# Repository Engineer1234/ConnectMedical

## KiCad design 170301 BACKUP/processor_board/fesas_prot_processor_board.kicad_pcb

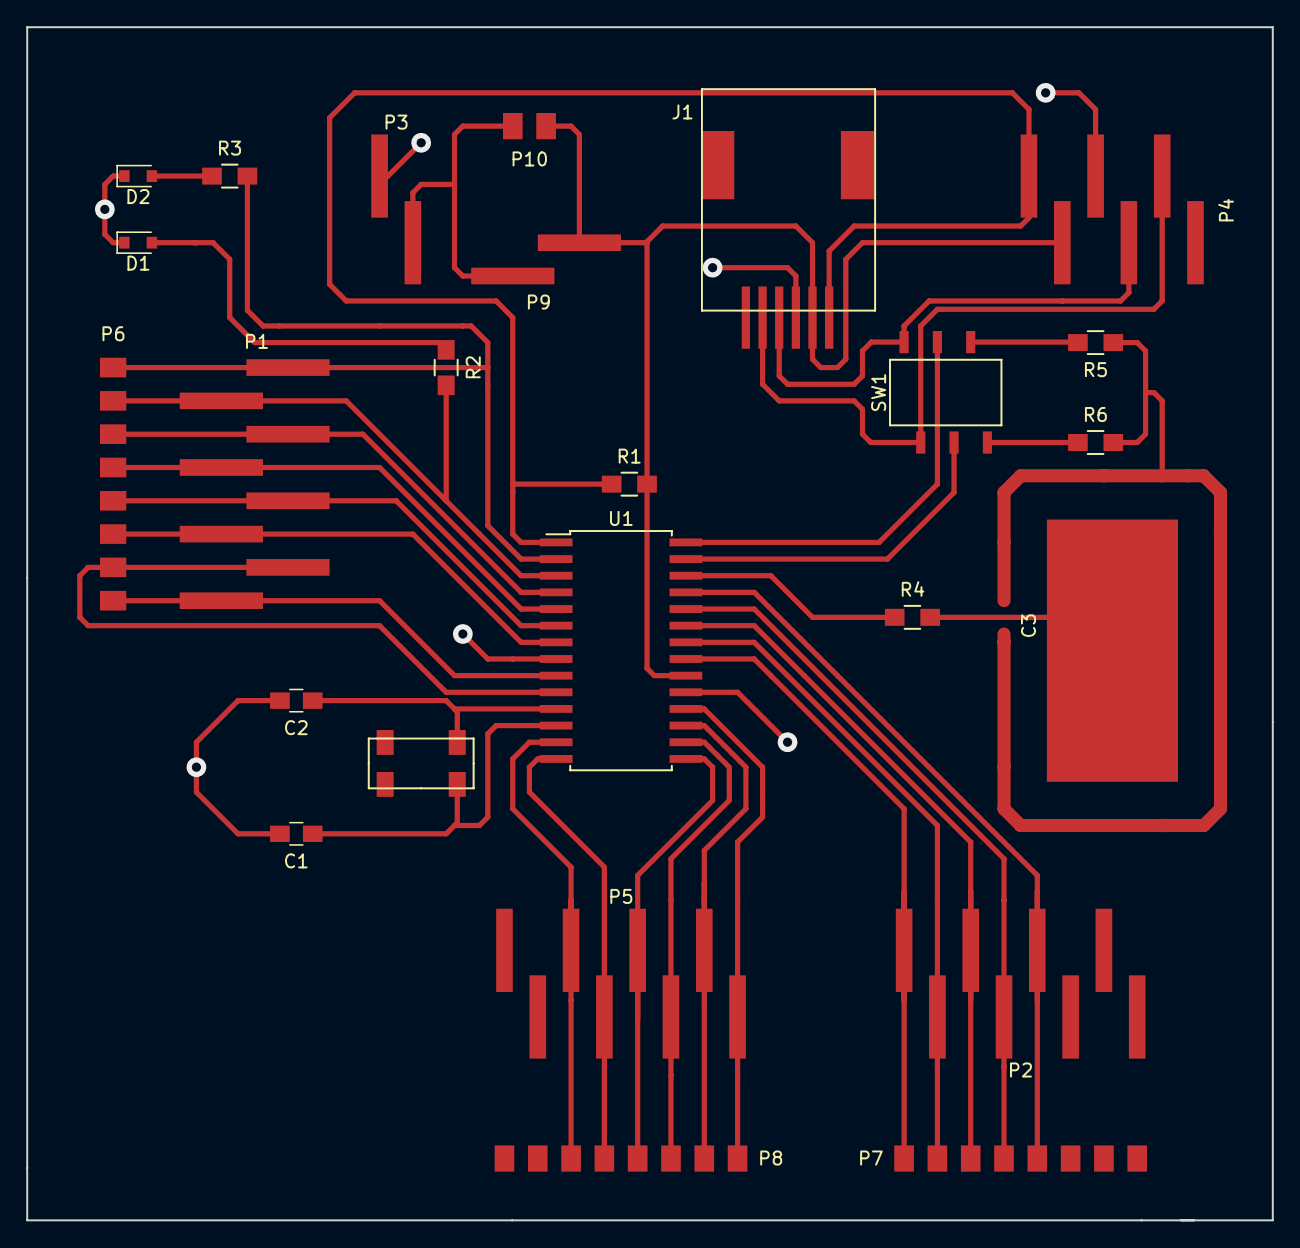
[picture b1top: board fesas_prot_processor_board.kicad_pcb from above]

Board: 2 copper layers, 95.0 x 91.0 mm, 25 parts (0 on the bottom side), 36 nets.

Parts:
C1, C2: 5pF; C_0805_HandSoldering
C3: cap_sense_pad; Capsense_Pad
D1, D2: LED; D_0805
J1: RJ11; RJ11_SMD_Socket
P1, P2, P5: CONN_01X08; Sullins_SMD_pin_header_1x8_GBC36SABN-M30
P3, P9: CONN_01X02; Sullins_SMD_pin_header_1x2_GBC36SABN-M30
P4: CONN_01X06; Sullins_SMD_pin_header_1x6_GBC36SABN-M30
P6, P7, P8: CONN_01X08; wire_solder_pad_2.54mm_1x8
P10: CONN_01X02; wire_solder_pad_2.54mm_1x2
R1: 50k; R_0805_HandSoldering
R2, R3, R4, R5, R6: R; R_0805_HandSoldering
SW1: NKKswitches_G3T22AP; NKKSwitches_G3T22AP
U1: PIC16(L)F1512-I/SO; SOIC-28W_7.5x17.9mm_Pitch1.27mm
Y1: Abracon_ABS25

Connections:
/CAP_SENSOR: R4.1, U1.26
/Guard_trace: R5.1, R6.2
/MCLR/Vpp: J1.1, P4.1, R1.1, U1.1
/PGC(ICSPCLK): J1.5, P4.5, SW1.3
/PGD(ICSPDAT): J1.4, P4.4, SW1.6
GND: C1.2, C2.2, D1.1, D2.1, J1.3, P3.1, P4.3, U1.8, U1.19
unnamed: C1.1, U1.12, Y1.4
unnamed: C2.1, U1.11, Y1.1
unnamed: C3.1, R4.2
unnamed: D1.2, R2.1
unnamed: D2.2, R3.1
unnamed: P1.1, P6.1, U1.9
unnamed: P1.2, P6.2, U1.10
unnamed: P1.3, P6.3, U1.7
unnamed: P1.4, P6.4, U1.6
unnamed: P1.5, P6.5, U1.5
unnamed: P1.6, P6.6, U1.4
unnamed: P1.7, P6.7, R2.2, U1.3
unnamed: P1.8, P6.8, R3.2, U1.2
unnamed: P2.4, P7.4, U1.25
unnamed: P2.5, P7.5, U1.24
unnamed: P2.6, P7.6, U1.23
unnamed: P2.7, P7.7, U1.22
unnamed: P2.8, P7.8, U1.21
unnamed: P5.3, P8.3, U1.13
unnamed: P5.4, P8.4, U1.14
unnamed: P5.5, P8.5, U1.15
unnamed: P5.6, P8.6, U1.16
unnamed: P5.7, P8.7, U1.17
unnamed: P5.8, P8.8, U1.18
unnamed: P3.2, P9.1, P10.2
unnamed: R5.2, SW1.4
unnamed: R6.1, SW1.1
unnamed: SW1.2, U1.27
unnamed: SW1.5, U1.28
VDD: J1.2, P4.2, P9.2, P10.1, R1.2, U1.20

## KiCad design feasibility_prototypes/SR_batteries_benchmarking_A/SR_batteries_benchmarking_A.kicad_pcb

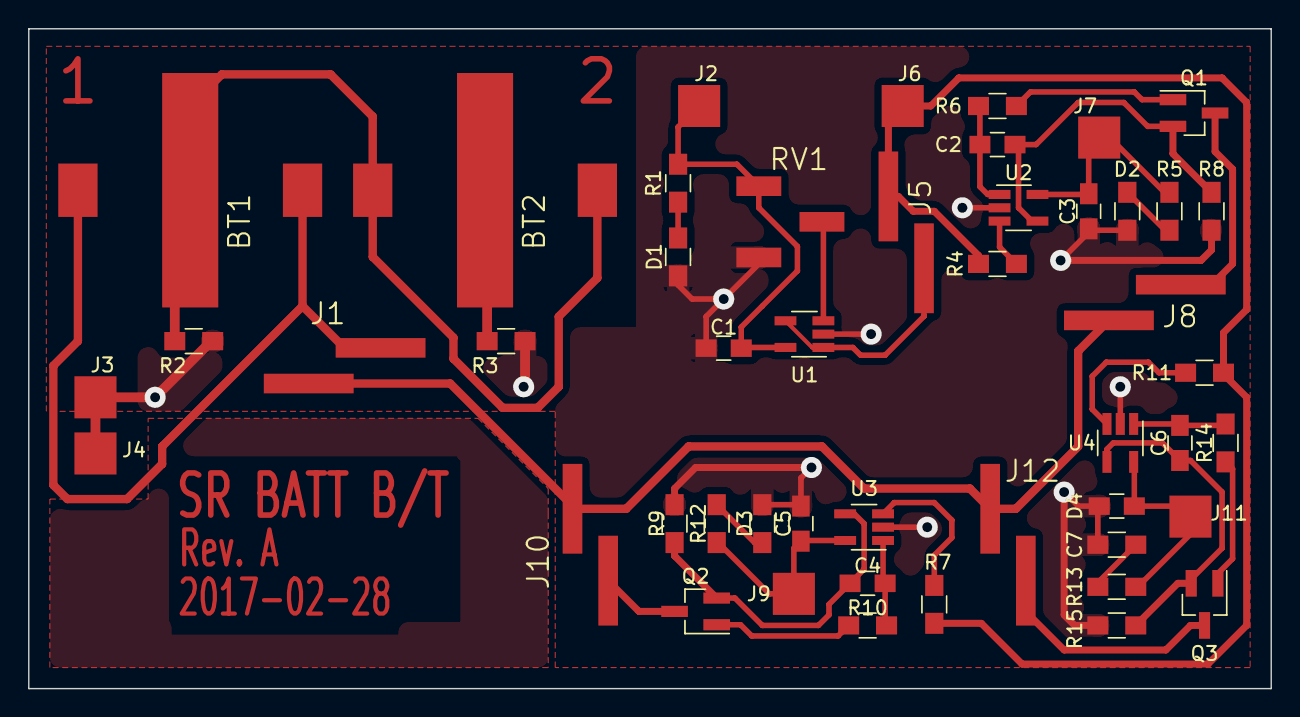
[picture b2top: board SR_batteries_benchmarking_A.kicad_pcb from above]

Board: 2 copper layers, 88.5 x 47.0 mm, 48 parts (0 on the bottom side), 31 nets.

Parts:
BT1: Cell1; proto_sm_coin_cell_holder-2996-2993
BT2: Cell2; proto_sm_coin_cell_holder-2996-2993
C1, C3, C5, C7: 0.1u; C_0805_HandSoldering
C2, C4, C6: C; C_0805_HandSoldering
D1: RED; R_0805_HandSoldering
D2: WHT; R_0805_HandSoldering
D3: GRN; R_0805_HandSoldering
D4: YLW; R_0805_HandSoldering
J1: Current Measurement; proto_smd_header-1x2-2.54mm-G_C__SABN_M30
J2: EN_POT; proto_smd_pad-sq.-3mm
J3, J4: GND; proto_smd_pad-sq.-3mm
J5, J8, J10, J12: Jumper; proto_smd_header-1x2-2.54mm-G_C__SABN_M30
J6: VIN; proto_smd_pad-sq.-3mm
J7: EN_HIGH_CURR; proto_smd_pad-sq.-3mm
J9: EN_LOW_CURR; proto_smd_pad-sq.-3mm
J11: EN_MED_CURR; proto_smd_pad-sq.-3mm
Q1, Q2, Q3: BSH103; SOT-23_Handsoldering
R1, R13: 680; R_0805_HandSoldering
R2, R3, R4, R6, R7, R10, R11, R14: 0; R_0805_HandSoldering
R5, R9: 390; R_0805_HandSoldering
R8: RLH; R_0805_HandSoldering
R12: RLL; R_0805_HandSoldering
R15: RLM; R_0805_HandSoldering
RV1: 500k; proto_smd_pot-model_84w
U1, U2, U3, U4: MCP601; SOT-23-5_HandSoldering

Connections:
/BATT+: J1.2, J8.1, J10.1, J12.1
/VIN: J5.2, J6.1, R4.2, R7.2, R11.2
GND: C1.2, C3.2, C5.2, C7.2, D1.1, D2.1, D3.1, D4.1, J3.1, J4.1, R2.2, R3.2, R8.1, R12.1, R15.1, RV1.3, U1.2, U2.2, U3.2, U4.2
unnamed: BT1.1, BT1.2, J1.1
unnamed: BT1.3, BT2.1, BT2.2, R2.1
unnamed: BT2.3, R3.1
unnamed: C1.1, J2.1, R1.1, RV1.1, U1.5
unnamed: C2.1, Q1.2, R8.2, U2.4
unnamed: C2.2, R6.2, U2.1
unnamed: C3.1, J7.1, R5.1, U2.5
unnamed: C4.1, Q2.2, R12.2, U3.4
unnamed: C4.2, R10.2, U3.1
unnamed: C5.1, J9.1, R9.1, U3.5
unnamed: C6.1, Q3.2, R15.2, U4.4
unnamed: C6.2, R14.2, U4.1
unnamed: C7.1, J11.1, R13.1, U4.5
unnamed: D1.2, R1.2
unnamed: D2.2, R5.2
unnamed: D3.2, R9.2
unnamed: D4.2, R13.2
unnamed: J5.1, U1.1, U1.4
unnamed: J8.2, Q1.3
unnamed: J10.2, Q2.3
unnamed: J12.2, Q3.3
unnamed: Q1.1, R6.1
unnamed: Q2.1, R10.1
unnamed: Q3.1, R14.1
unnamed: R4.1, U2.3
unnamed: R7.1, U3.3
unnamed: R11.1, U4.3
unnamed: RV1.2, U1.3

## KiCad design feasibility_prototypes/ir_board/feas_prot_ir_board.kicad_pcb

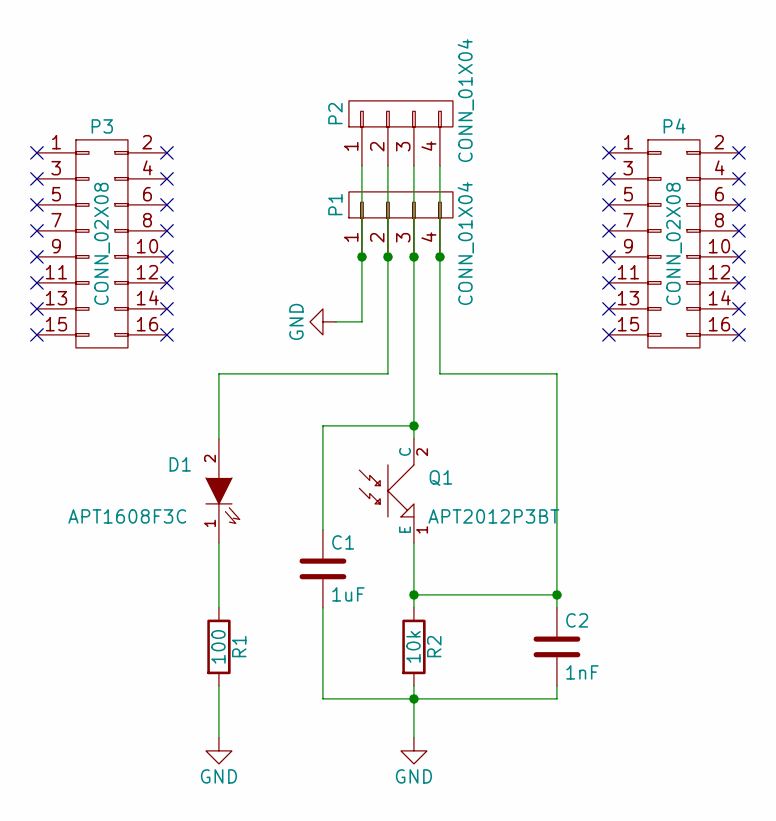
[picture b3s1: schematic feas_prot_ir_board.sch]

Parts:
C1: 1uF; C_0805_HandSoldering
C2: 1nF; C_0805_HandSoldering
D1: APT1608F3C; LED_APT1608F3C
P1, P2: CONN_01X04
P3, P4: CONN_02X08; Sullins_SMD_2x08_NPTC082KFMS-RC
Q1: APT2012P3BT; Phototransistor_APT2012P3BT
R1: 100; R_0805_HandSoldering
R2: 10k; R_0805_HandSoldering

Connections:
GND: C1.2, C2.2, P1.1, P2.1, R1.2, R2.2
unnamed: C1.1, P1.3, P2.3, Q1.2 (C)
unnamed: C2.1, P1.4, P2.4, Q1.1 (E), R2.1
unnamed: D1.1 (K), R1.1
unnamed: D1.2 (A), P1.2, P2.2

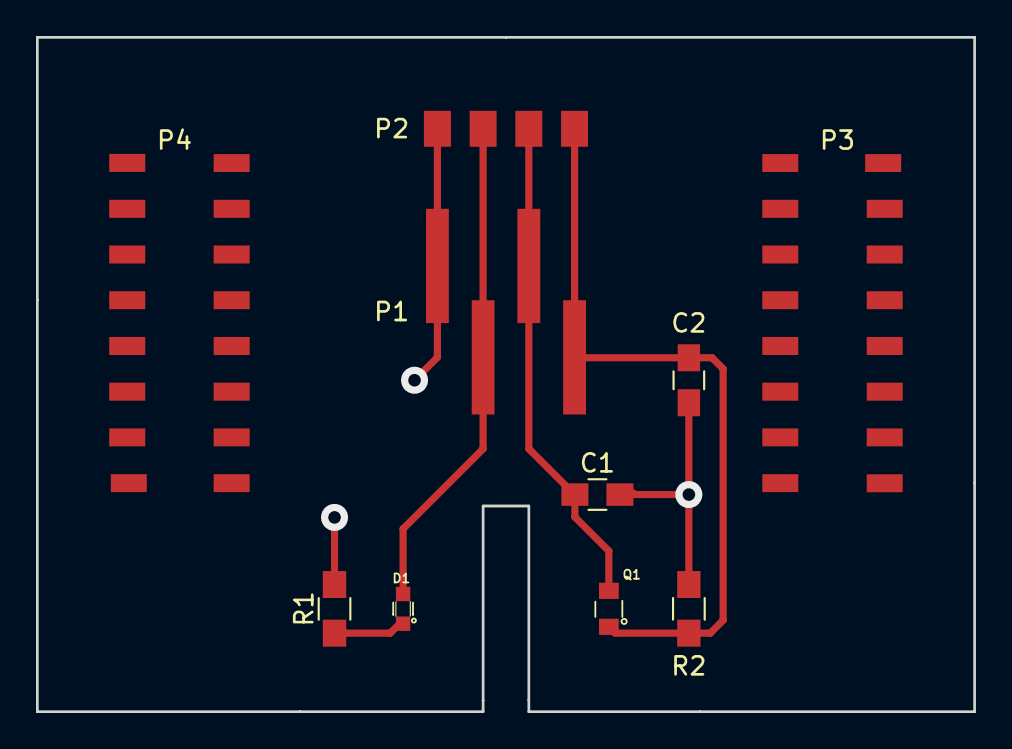
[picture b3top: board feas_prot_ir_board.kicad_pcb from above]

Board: 2 copper layers, 52.1 x 37.5 mm, 10 parts (0 on the bottom side), 5 nets.
